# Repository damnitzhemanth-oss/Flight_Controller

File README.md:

# FLIGHT CONTROLLER - STM32F405

A custom 4 layer flight controller built from scratch for YSWS Pixl. This follows a hybrid approach of 50mm*50mm which is not normal for actual FCs on drone. This is only a **paper-design**. This has not been manufactured yet.

# Description 
This flight controller is unique in a way, unlike most of the FC's which skip Fuses to save space, this contains 3 fuses, making the room for human errors tiny.

The main MCU is STM32F405RGT6, this tiny thing has 1MB flash and 192KB ram and can easily run betaflight at full speed. With betaflight it can also do blackbox (memory) logging, IMU (gyroscope) and OSD (share details like altitude etc) simultaneously.

IMU I used for this project is ICM-42688-P which runs at 24 MHZ! It's a 6 axis gyroscope. I chose this because it is low noise (doesn't give false readings due to electrical noise) and gives reading in high resolution.

Then comes the blackbox which logs the data which is useful when the drone crashes or something so it is easier for us to point out errors. The exact module is W25Q128JVS,
~4 minutes of 2 kHz blackbox logging, or ~30 minutes at 500 Hz.

Watchdog-safe boot BOOT0 pull-down (R21) + BOOT1 pull-down (R25) MCU always boots from flash unless user says so. Sometimes when drone crashes MCU might repeatedly boot into USB mode and face continuous resets, but this mechanism ensures that, this aint going to happen.

No OSD: OSD is a chip that transmits data like altitude etc into the video, but most of the modern day digital cameras have this inbuilt. So I removed it.

No barometer: Same as OSD, most modern day GPS have barometer built in so there is no need of one on board.

2S - 6S input power, max 28V. And over current protection in built.

Reverse polarity protection,due to a P-FET on board even if the user connects + and - in reverse, power ain't gonna reach other parts,it's gonna stop at the P-Fet thus protecting rest of the FC.

USB ORing protection, with schkotty diode it ensures that USB and battery power won't fight or push power back.

5 independent UARTs, enough for connections GPS, Camera, etc with one spare.

4 pins for motors, with current and voltage measurement with dividers (a divider is a junction of Resistors which steps down the voltage/current and MCU multiplies it with a specific number,here 11 to get voltage and current readings).

Addressable RGB LED and two onboard LEDs indicating 5V and 3.3V with buzzer connections headers for audible output.

What makes it unique ? I built this board such that it is easy to debug, yes no board can work perfectly first time, this instead of saving space, i tried to make it more debuggable by adding multiple Testpoints. 

# Overview

This FC contains minimal architecture (as i am a rookie), it does not contain in built barometer or OSD.

# Architecture

```
Flight_Controller
├── PCB
│   ├── FlightController_Drone.csv
│   ├── FlightController_Drone.kicad_pcb
│   ├── FlightController_Drone.kicad_pro
│   ├── FlightController_Drone.kicad_sch
│   └── gerbers.zip
├── README.md
└── images
    ├── DRAFT
    │   ├── S10_2.png
    │   ├── S11_2.png
    │   ├── S12_2.png
    │   ├── S13_2.png
    │   ├── S1_1.png
    │   ├── S2_1.png
    │   ├── S3_1.png
    │   ├── S4_2.png
    │   ├── S4_P.png
    │   ├── S5_2.png
    │   ├── S6_2.png
    │   ├── S7_2.png
    │   ├── S8_2.png
    │   ├── S9_2.png
    │   └── SFull_2.png
    └── FINAL
        ├── 3D_PCB.png
        ├── 3D_PCB_B.png
        ├── 3D_PCB_HERO.png
        ├── Annotation 2026-10-11 182149.png
        ├── B_CU_PCB.png
        ├── DRC_DUMB.png
        ├── F_CU_PCB.png
        ├── F_PCB.png
        ├── In1_CU.png
        ├── In2_CU.png
        ├── S1.png
        ├── S10.png
        ├── S11.png
        ├── S12.png
        ├── S13.png
        ├── S2.png
        ├── S3.png
        ├── S4.png
        ├── S5.png
        ├── S6.png
        ├── S7.png
        ├── S8.png
        └── S9.png
```

# BOM
refer the .csv file in this repo under PCB.

# Gallery

**FOR MORE IMAGES PLEASE CHECK images FOLDER**  

# Note

DRC is giving weird errors about footprints touching each other which is fine until pads touch, so I moved them into warnings.

# AI usage
Ai was used only in one or two instances to verify netlist, this makes AI usage less than 5% for this project.

# License

MIT License and you are free to manufacture this board (ik no one will) but in case it dont work, inform me :)

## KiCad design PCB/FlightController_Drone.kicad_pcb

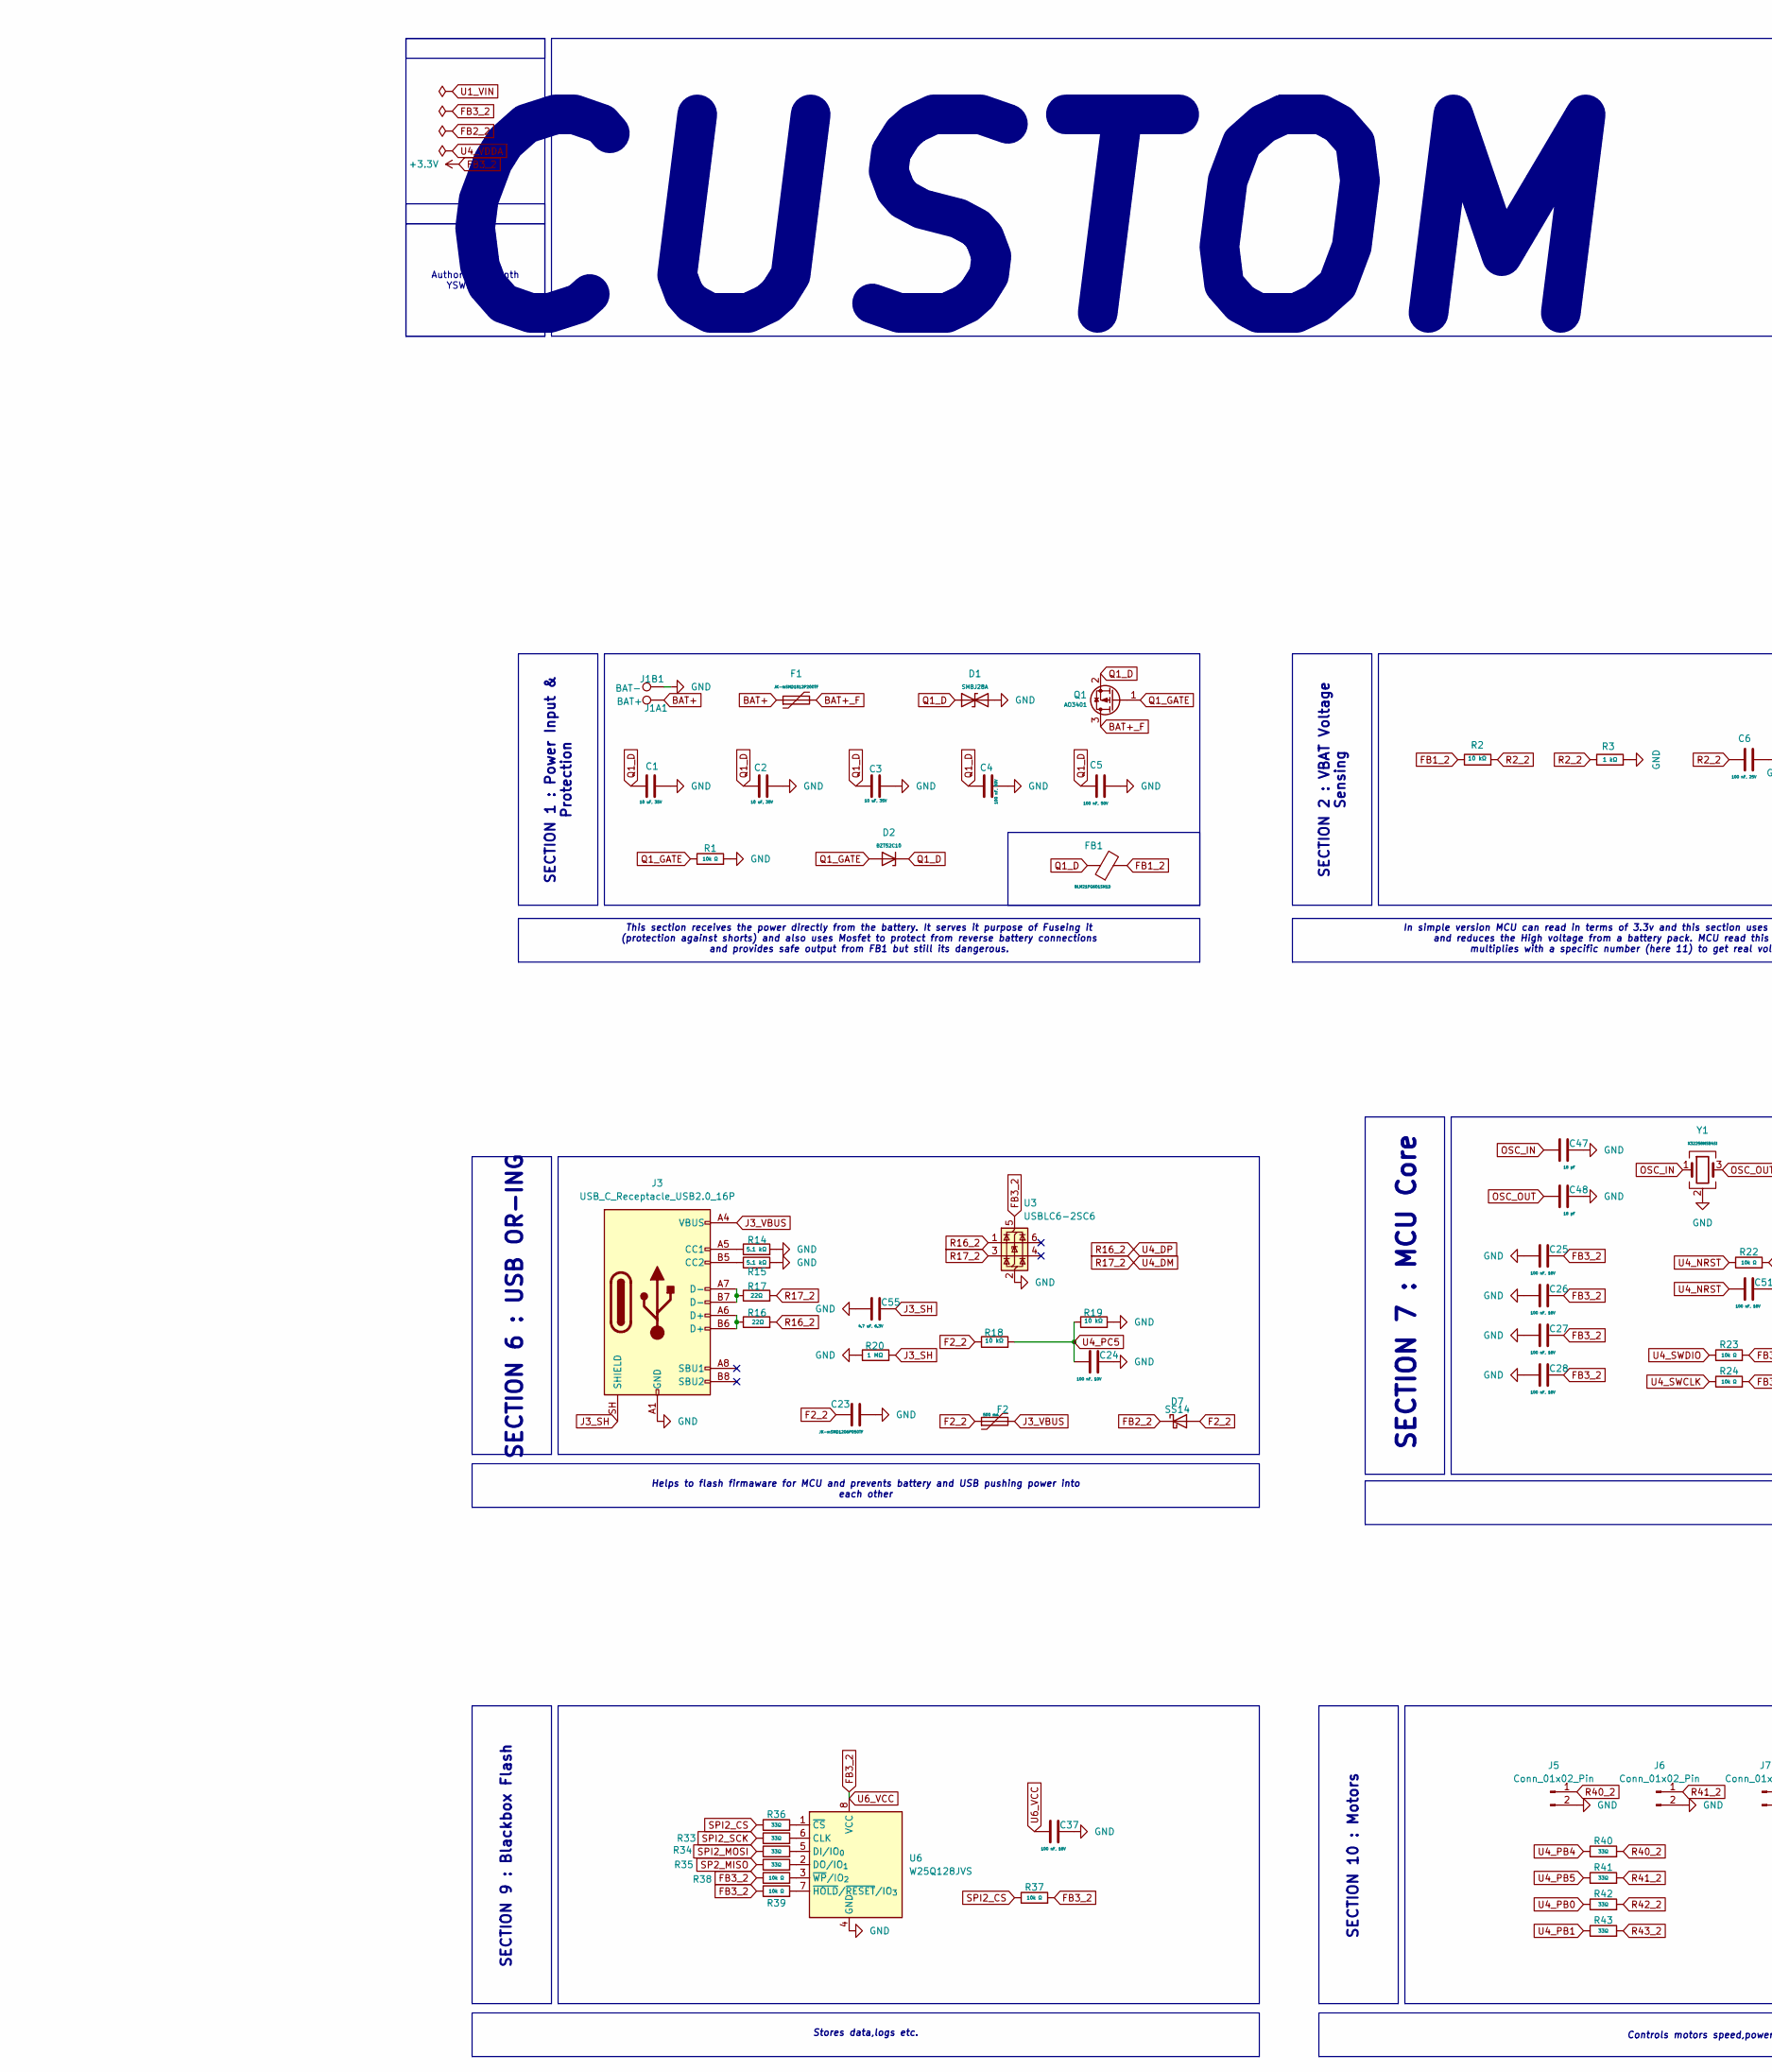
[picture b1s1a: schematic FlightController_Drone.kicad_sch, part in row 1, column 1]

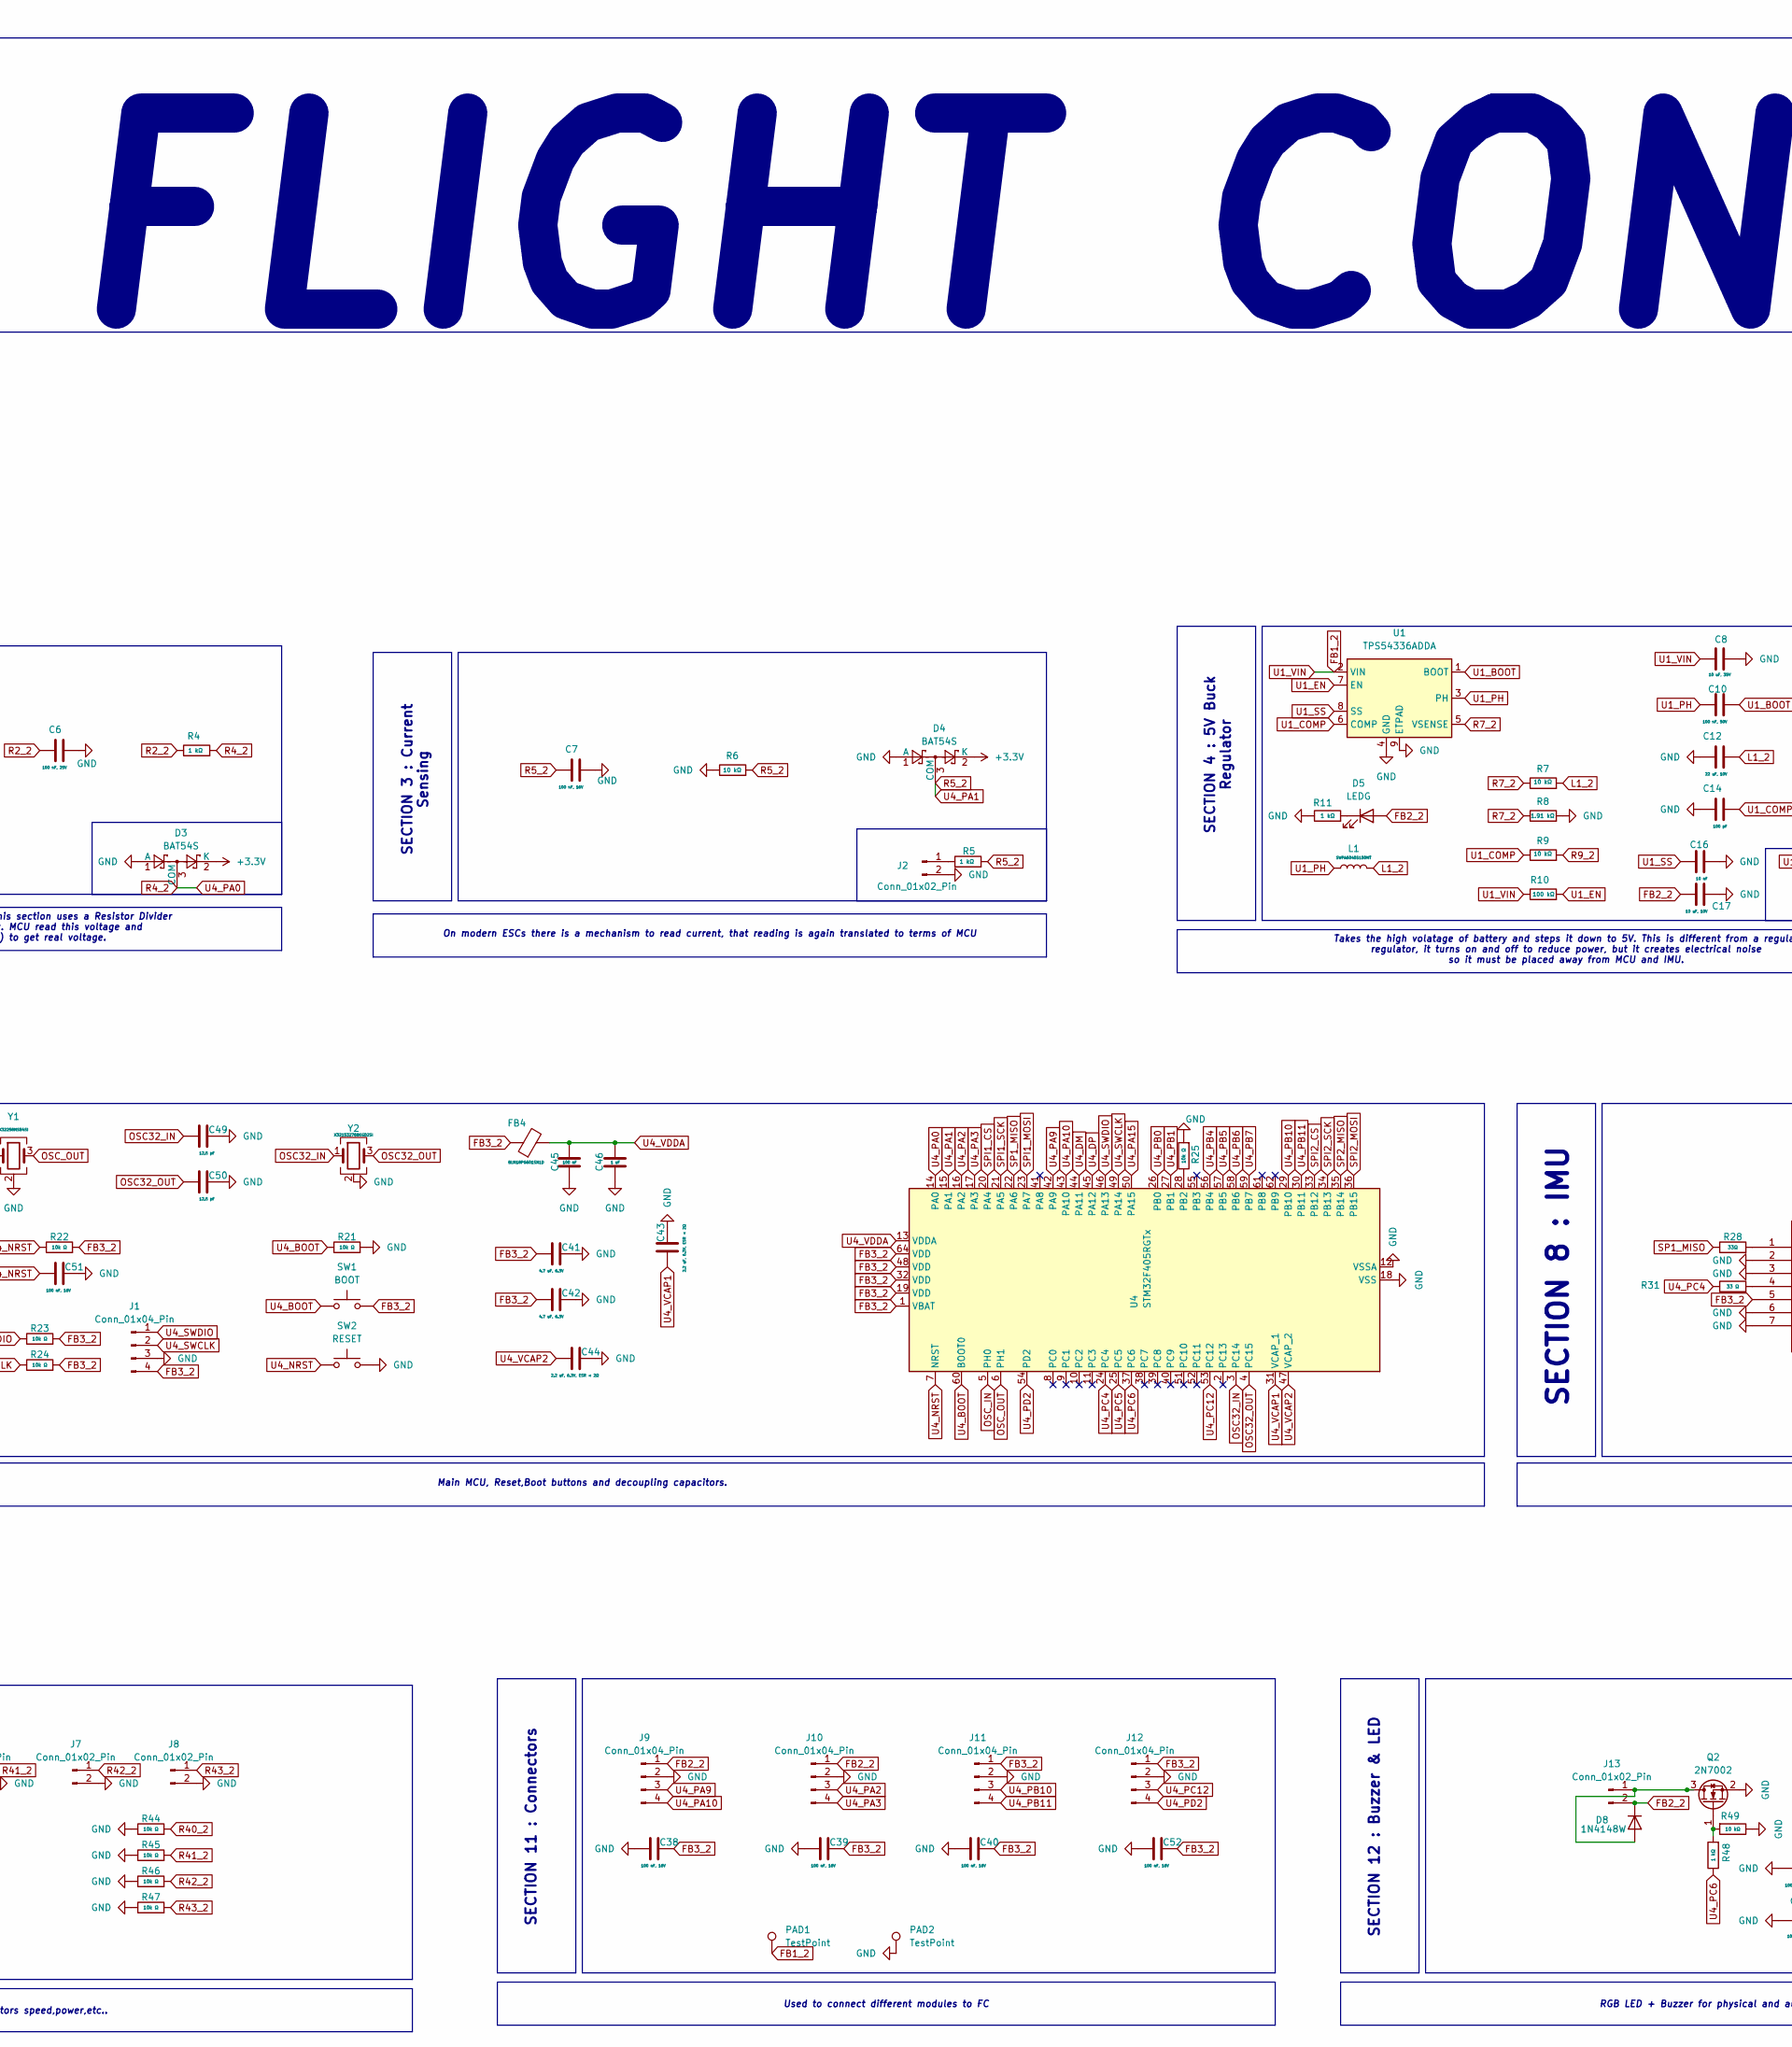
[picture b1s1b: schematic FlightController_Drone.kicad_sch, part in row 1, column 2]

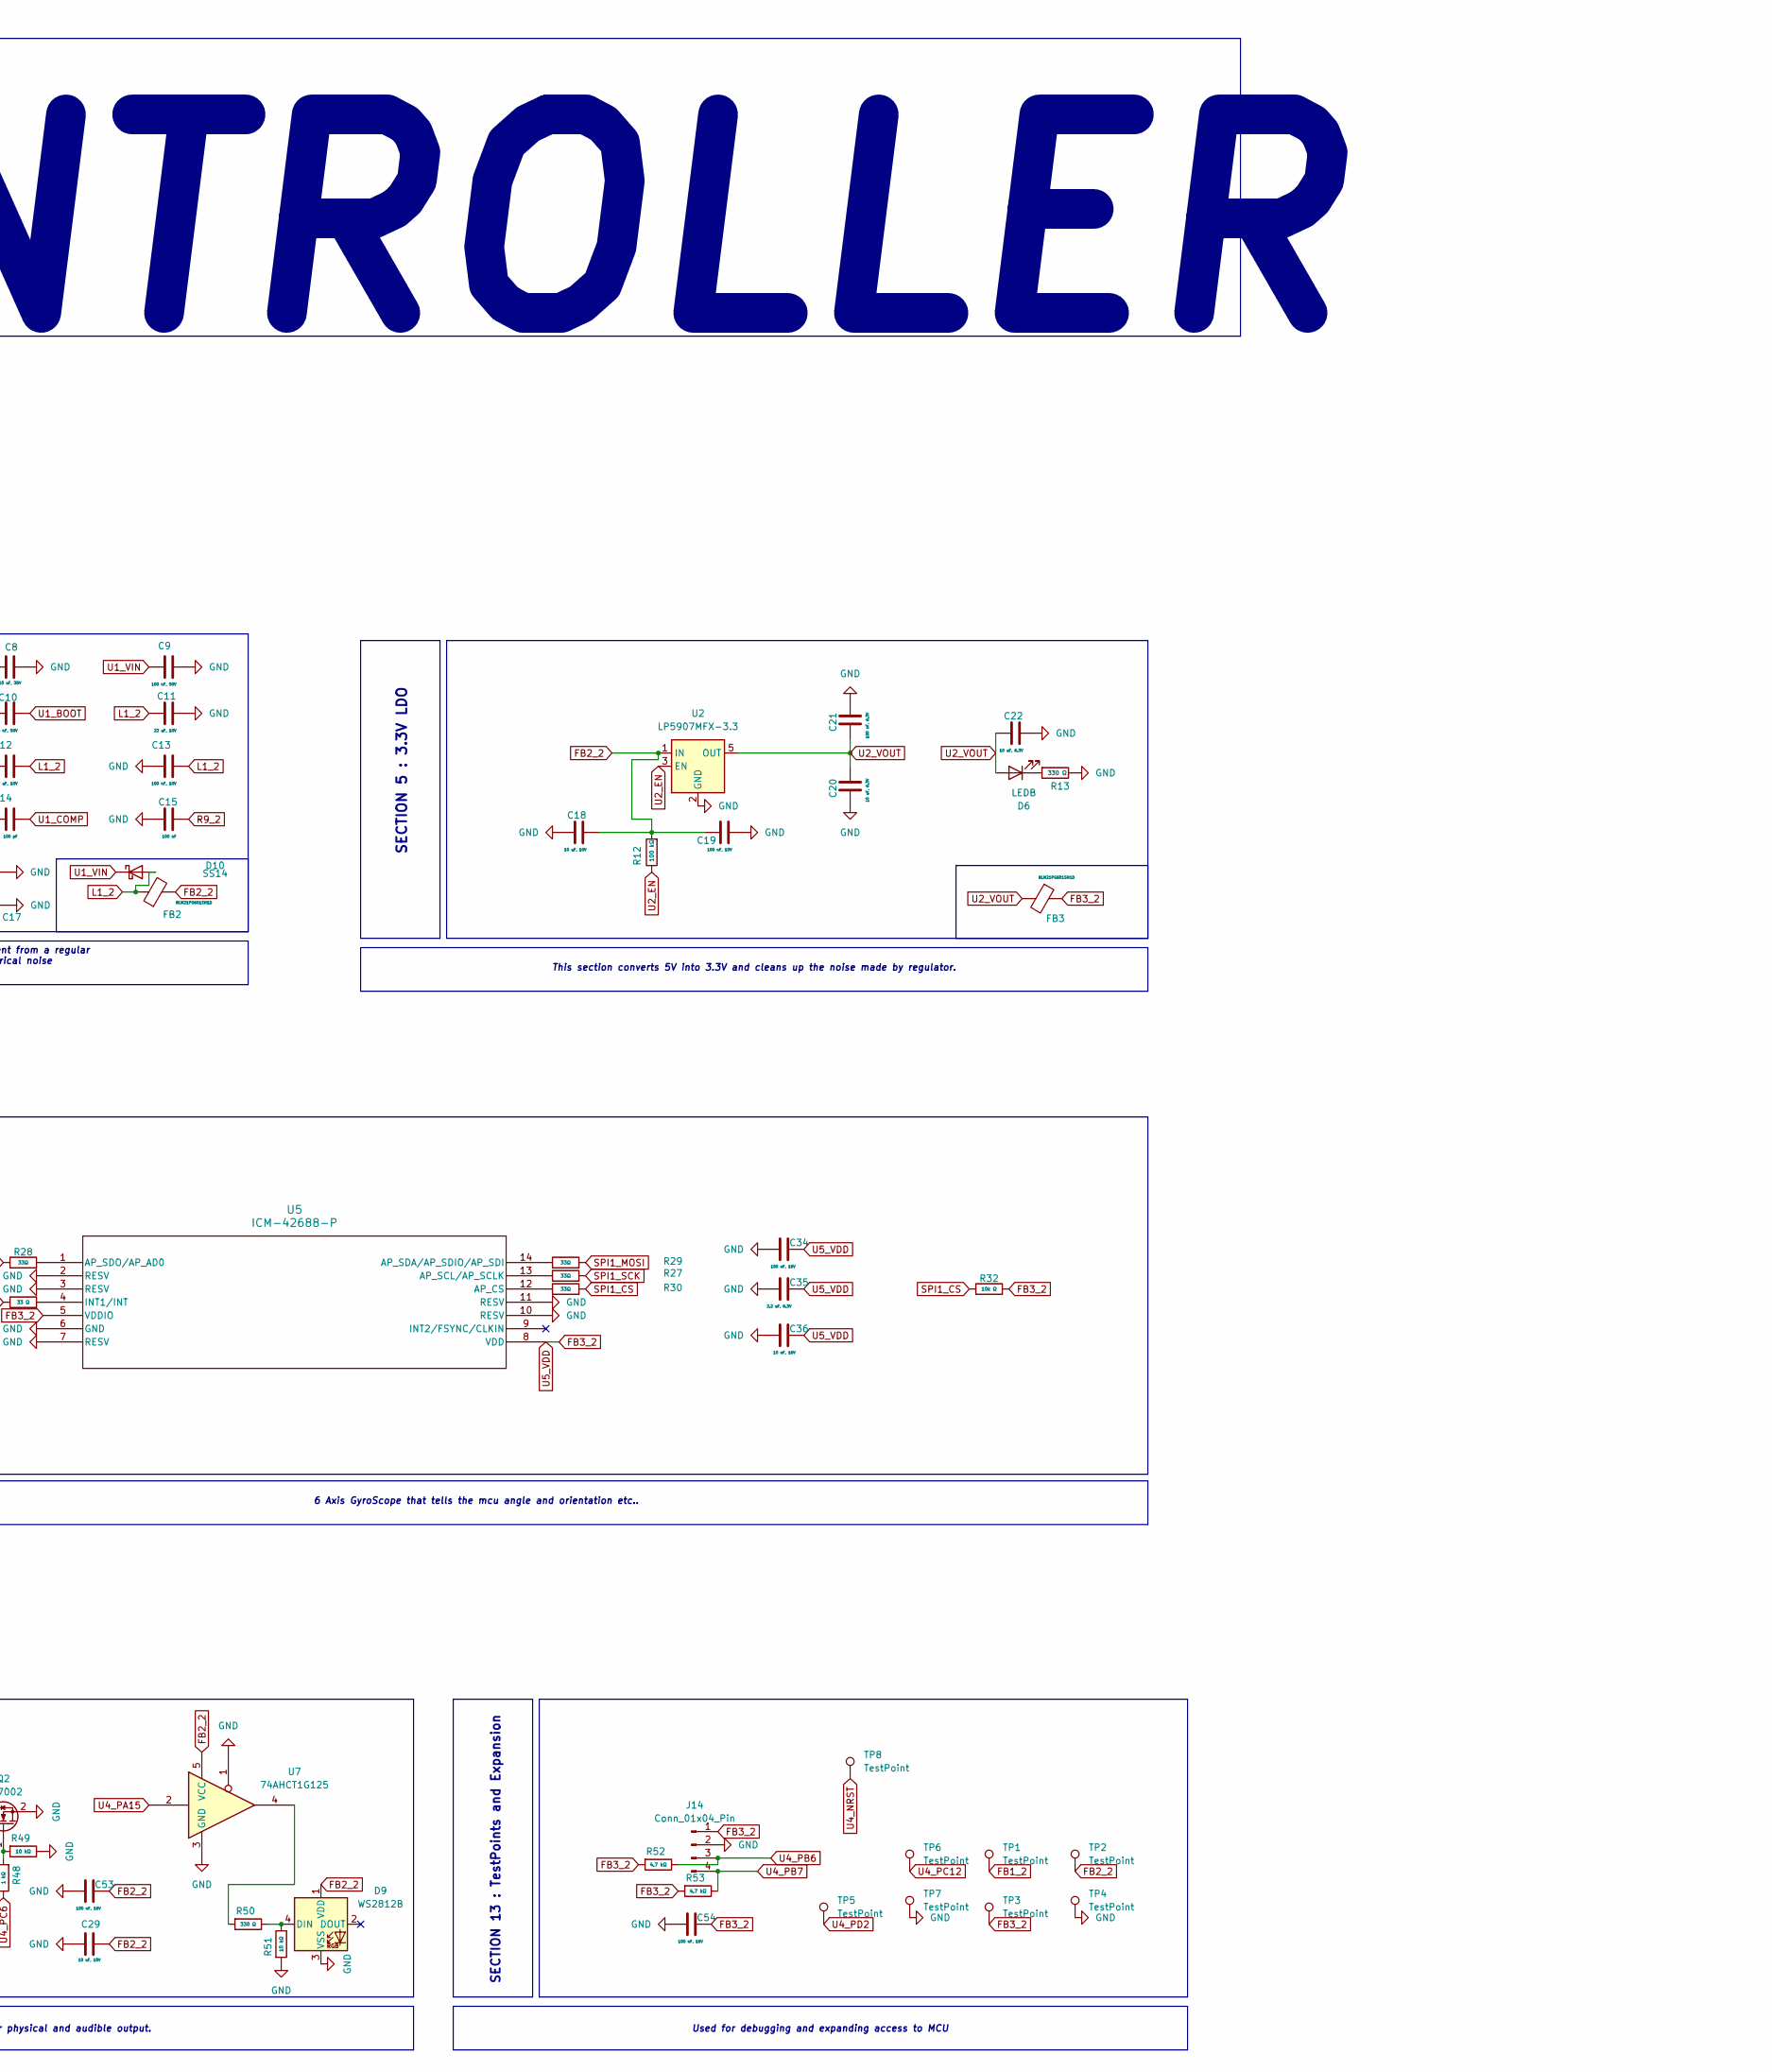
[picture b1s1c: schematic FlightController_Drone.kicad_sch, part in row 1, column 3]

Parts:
C1, C2, C3, C8: 10 uF, 35V; C_1206_3216Metric
C4, C5, C9, C10: 100 nF, 50V; C_0603_1608Metric
C6: 100 nF, 25V; C_0603_1608Metric
C7: 100 nF, 16V; C_0603_1608Metric
C11, C12: 22 uF, 10V; C_0805_2012Metric
C13, C19, C24: 100 nF, 10V; C_0603_1608Metric
C14: 100 pF; C_0603_1608Metric
C15: 100 nF; C_0603_1608Metric
C16: 10 nF; C_0603_1608Metric
C17, C18: 10 uF, 10V; C_0805_2012Metric
C20, C22: 10 uF, 6.3V; C_0805_2012Metric
C21: 100 nF, 6.3V; C_0805_2012Metric
C23: JK-mSMD1206P050TF; C_0603_1608Metric
C25, C26, C27, C28, C34, C37, C38, C39, C40, C51, C52, C53, C54: 100 nF, 16V; C_0402_1005Metric
C29: 10 uF, 10V; C_1206_3216Metric
C35: 2.2 uF, 6.3V; C_0603_1608Metric
C36: 10 nF, 16V; C_0402_1005Metric
C41, C42, C55: 4.7 uF, 6.3V; C_0603_1608Metric
C43, C44: 2.2 uF, 6.3V, ESR < 2Ω; C_0603_1608Metric
C45: 100 nF; C_0402_1005Metric
C46: 1 uF; C_0603_1608Metric
C47, C48: 18 pF; C_0402_1005Metric
C49, C50: 12.5 pF; C_0402_1005Metric
D1: SMBJ28A; D_SMB
D2: BZT52C10; D_SOD-323
D3, D4: BAT54S; SOT-23
D5: LEDG; LED_0603_1608Metric
D6: LEDB; LED_0603_1608Metric
D7, D10: SS14; D_SOD-323
D8: 1N4148W; D_SOD-323
D9: WS2812B; LED_WS2812B_PLCC4_5.0x5.0mm_P3.2mm
F1: JK-mSMD1812P200TF; Fuse_1812_4532Metric
F2: 500 mA; Fuse_1812_4532Metric
FB1, FB2, FB3: BLM21PG601SN1D; L_0805_2012Metric
FB4: BLM18PG601SN1D; L_0805_2012Metric
J1: Conn_01x04_Pin; PinHeader_1x04_P1.27mm_Vertical
J1A1: BAT+; TestPoint_Pad_D3.0mm
J1B1: BAT-; TestPoint_Pad_D3.0mm
J2, J5, J6, J7, J8, J13: Conn_01x02_Pin; PinHeader_1x02_P2.54mm_Vertical
J3: USB_C_Receptacle_USB2.0_16P; USB_C_Receptacle_HCTL_HC-TYPE-C-16P-01A
J9, J10, J11, J12, J14: Conn_01x04_Pin; JST_SH_SM04B-SRSS-TB_1x04-1MP_P1.00mm_Horizontal
L1: SWPA6045S150MT; L_6.3x6.3_H3
PAD1, PAD2: TestPoint; TestPoint_Pad_D2.0mm
Q1: AO3401; SOT-23
Q2: 2N7002; SOT-23
R1, R21, R22, R23, R24, R25, R32, R37, R38, R39, R44, R45, R46, R47: 10k Ω; R_0603_1608Metric
R2, R6, R7, R9, R18, R19: 10 kΩ; R_0603_1608Metric
R3, R4, R5, R11: 1 kΩ; R_0603_1608Metric
R8: 1.91 kΩ; R_0603_1608Metric
R10, R12: 100 kΩ; R_0603_1608Metric
R13: 330 Ω; R_0603_1608Metric
R14, R15: 5.1 kΩ; R_0603_1608Metric
R16, R17: 22Ω; R_0603_1608Metric
R20: 1 MΩ; R_0603_1608Metric
R27, R28, R29, R30, R33, R34, R35, R36, R40, R41, R42, R43: 33Ω; R_0402_1005Metric
R31: 33 Ω; R_0603_1608Metric
R48: 1 kΩ; R_0402_1005Metric
R49, R51: 10 kΩ; R_0402_1005Metric
R50: 330 Ω; R_0402_1005Metric
R52, R53: 4.7 kΩ; R_0402_1005Metric
SW1: BOOT; SW_SPST_TL3342
SW2: RESET; SW_SPST_TL3342
TP1, TP2, TP3, TP4, TP5, TP6, TP7, TP8: TestPoint; TestPoint_Pad_D1.5mm
U1: TPS54336ADDA; TI_SO-PowerPAD-8_ThermalVias
U2: LP5907MFX-3.3; SOT-23-5
U3: USBLC6-2SC6; SOT-23-6
U4: STM32F405RGTx; LQFP-64_10x10mm_P0.5mm
U5: ICM-42688-P; LGA14_2P5X3X0P91_TDK
U6: W25Q128JVS; SOIC-8_5.3x5.3mm_P1.27mm
U7: 74AHCT1G125; SOT-353_SC-70-5
Y1: X32258MSB4SI; Crystal_SMD_3225-4Pin_3.2x2.5mm
Y2: X321532768KGD2SI; Crystal_SMD_3225-4Pin_3.2x2.5mm

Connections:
BAT+: F1.1, J1A1.1 (1_1)
BAT+_F: F1.2, Q1.3 (D)
F2_2: C23.1, D7.2 (A), F2.1, R18.1
FB1_2: C8.1, C9.1, D10.1 (K), FB1.2, PAD1.1 (1_1), R2.1, R10.1, TP1.1 (1_1), U1.2 (VIN)
FB2_2: C17.1, C18.2, C19.1, C29.2, C53.2, D5.2 (A), D7.1 (K), D8.1 (K), D9.1 (VDD), FB2.2, J9.1, J10.1, J13.2, R12.2, TP2.1 (1_1), U2.1 (IN), U7.5 (VCC)
FB3_2: C25.2, C26.2, C27.2, C28.2, C34.2, C35.2, C36.2, C37.1, C38.2, C39.2, C40.2, C41.1, C42.1, C52.2, C54.2, D3.2 (K), D4.2 (K), FB3.1, FB4.1, J1.4, J11.1, J12.1, J14.1, R22.2, R23.2, R24.2, R32.2, R37.2, R38.1, R39.1, R52.2, R53.2, SW1.2, TP3.1 (1_1), U3.5 (VBUS), U4.1 (VBAT), U4.19 (VDD), U4.32 (VDD), U4.48 (VDD), U4.64 (VDD), U5.5 (VDDIO), U5.8 (VDD), U6.8 (VCC)
GND: C1.2, C2.2, C3.2, C4.2, C5.2, C6.2, C7.2, C8.2, C9.2, C11.2, C12.1, C13.1, C14.1, C15.1, C16.2, C17.2, C18.1, C19.2, C20.1, C21.2, C22.2, C23.2, C24.2, C25.1, C26.1, C27.1, C28.1, C29.1, C34.1, C35.1, C36.1, C37.2, C38.1, C39.1, C40.1, C41.2, C42.2, C43.2, C44.2, C45.1, C46.1, C47.2, C48.2, C49.2, C50.2, C51.2, C52.1, C53.1, C54.1, C55.1, D1.2 (A2), D3.1 (A), D4.1 (A), D9.3 (VSS), J1.3, J1B1.1 (1_1), J2.2, J3.A1 (GND), J3.A12 (GND), J3.B1 (GND), J3.B12 (GND), J5.2, J6.2, J7.2, J8.2, J9.2, J10.2, J11.2, J12.2, J14.2, PAD2.1 (1_1), Q2.2 (S), R1.2, R3.2, R6.1, R8.2, R11.1, R13.1, R14.2, R15.2, R19.2, R20.1, R21.2, R25.2, R44.1, R45.1, R46.1, R47.1, R49.1, R51.2, SW2.2, TP4.1 (1_1), TP7.1 (1_1), U1.4 (GND), U1.9 (ETPAD), U2.2 (GND), U3.2 (GND), U4.12 (VSSA), U4.18 (VSS), U4.63 (VSS), U5.2 (RESV), U5.3 (RESV), U5.6 (GND), U5.7 (RESV), U5.10 (RESV), U5.11 (RESV), U6.4 (GND), U7.1, U7.3 (GND), Y1.2 (G), Y1.4 (G), Y2.2 (G), Y2.4 (G)
J3_SH: C55.2, J3.SH (SHIELD), R20.2
J3_VBUS: F2.2, J3.A4 (VBUS), J3.A9 (VBUS), J3.B4 (VBUS), J3.B9 (VBUS)
L1_2: C11.1, C12.2, C13.2, D10.2 (A), FB2.1, L1.2, R7.2
unnamed: D5.1 (K), R11.2
unnamed: D6.1 (K), R13.2
unnamed: D8.2 (A), J13.1, Q2.3 (D)
unnamed: D9.4 (DIN), R50.1, R51.1
unnamed: J2.1, R5.1
unnamed: J3.A5 (CC1), R14.1
unnamed: J3.B5 (CC2), R15.1
unnamed: J3.A6 (D+), J3.B6 (D+), R16.1
unnamed: J3.A7 (D-), J3.B7 (D-), R17.1
unnamed: Q2.1 (G), R48.2, R49.2
unnamed: R50.2, U7.4
unnamed: R25.1, U4.28 (PB2)
unnamed: R30.1, U5.12 (AP_CS)
unnamed: R27.1, U5.13 (AP_SCL/AP_SCLK)
unnamed: R29.1, U5.14 (AP_SDA/AP_SDIO/AP_SDI)
unnamed: R28.2, U5.1 (AP_SDO/AP_AD0)
unnamed: R31.2, U5.4 (INT1/INT)
unnamed: R33.2, U6.6 (CLK)
unnamed: R34.2, U6.5 (DI/IO_{0})
unnamed: R35.2, U6.2 (DO/IO_{1})
unnamed: R36.2, U6.1 (~CS)
unnamed: R39.2, U6.7 (~HOLD/~RESET/IO_{3})
unnamed: R38.2, U6.3 (~WP/IO_{2})
OSC32_IN: C49.1, U4.3 (PC14), Y2.1
OSC32_OUT: C50.1, U4.4 (PC15), Y2.3
OSC_IN: C47.1, U4.5 (PH0), Y1.1
OSC_OUT: C48.1, U4.6 (PH1), Y1.3
Q1_D: C1.1, C2.1, C3.1, C4.1, C5.1, D1.1 (A1), D2.1 (K), FB1.1, Q1.2 (S)
Q1_GATE: D2.2 (A), Q1.1 (G), R1.1
R2_2: C6.1, R2.2, R3.1, R4.1
R4_2: D3.3 (COM), R4.2, U4.14 (PA0)
R5_2: C7.1, D4.3 (COM), R5.2, R6.2, U4.15 (PA1)
R7_2: R7.1, R8.1, U1.5 (VSENSE)
R9_2: C15.2, R9.2
R16_2: R16.2, U3.1 (I/O1), U4.45 (PA12)
R17_2: R17.2, U3.3 (I/O2), U4.44 (PA11)
R40_2: J5.1, R40.2, R44.2
R41_2: J6.1, R41.2, R45.2
R42_2: J7.1, R42.2, R46.2
R43_2: J8.1, R43.2, R47.2
SP1_MISO: R28.1, U4.22 (PA6)
SP2_MISO: R35.1, U4.35 (PB14)
SPI1_CS: R30.2, R32.1, U4.20 (PA4)
SPI1_MOSI: R29.2, U4.23 (PA7)
SPI1_SCK: R27.2, U4.21 (PA5)
SPI2_CS: R36.1, R37.1, U4.33 (PB12)
SPI2_MOSI: R34.1, U4.36 (PB15)
SPI2_SCK: R33.1, U4.34 (PB13)
U1_BOOT: C10.2, U1.1 (BOOT)
U1_COMP: C14.2, R9.1, U1.6 (COMP)
U1_EN: R10.2, U1.7 (EN)
U1_PH: C10.1, L1.1, U1.3 (PH)
U1_SS: C16.1, U1.8 (SS)
U2_EN: R12.1, U2.3 (EN)
U2_VOUT: C20.2, C21.1, C22.1, D6.2 (A), FB3.2, U2.5 (OUT)
U4_BOOT: R21.1, SW1.1, U4.60 (BOOT0)
U4_NRST: C51.1, R22.1, SW2.1, TP8.1, U4.7 (NRST)
U4_PA2: J10.3, U4.16 (PA2)
U4_PA3: J10.4, U4.17 (PA3)
U4_PA9: J9.3, U4.42 (PA9)
U4_PA10: J9.4, U4.43 (PA10)
U4_PA15: U4.50 (PA15), U7.2
U4_PB0: R42.1, U4.26 (PB0)
U4_PB1: R43.1, U4.27 (PB1)
U4_PB4: R40.1, U4.56 (PB4)
U4_PB5: R41.1, U4.57 (PB5)
U4_PB6: J14.3, R52.1, U4.58 (PB6)
U4_PB7: J14.4, R53.1, U4.59 (PB7)
U4_PB10: J11.3, U4.29 (PB10)
U4_PB11: J11.4, U4.30 (PB11)
U4_PC4: R31.1, U4.24 (PC4)
U4_PC5: C24.1, R18.2, R19.1, U4.25 (PC5)
U4_PC6: R48.1, U4.37 (PC6)
U4_PC12: J12.3, TP6.1 (1_1), U4.53 (PC12)
U4_PD2: J12.4, TP5.1 (1_1), U4.54 (PD2)
U4_SWCLK: J1.2, R24.1, U4.49 (PA14)
U4_SWDIO: J1.1, R23.1, U4.46 (PA13)
U4_VCAP1: C43.1, U4.31 (VCAP_1)
U4_VCAP2: C44.1, U4.47 (VCAP_2)
U4_VDDA: C45.2, C46.2, FB4.2, U4.13 (VDDA)

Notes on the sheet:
SECTION 6 : USB OR-ING
SECTION 12 : Buzzer & LED
SECTION 4 : 5V Buck Regulator
SECTION 1 : Power Input & Protection
CUSTOM FLIGHT CONTROLLER
SECTION 3 : Current Sensing
SECTION 8 : IMU
SECTION 10 : Motors
SECTION 7 : MCU Core
SECTION 9 : Blackbox Flash
SECTION 2 : VBAT Voltage Sensing
SECTION 11 : Connectors
SECTION 5 : 3.3V LDO
Details
SECTION 13 : TestPoints and Expansion
Main MCU, Reset,Boot buttons and decoupling capacitors.
Helps to flash firmaware for MCU and prevents battery and USB pushing power into each other
In simple version MCU can read in terms of 3.3v and this section uses a Resistor Divider and reduces the High voltage from a battery pack. MCU read this voltage and multiplies with a specific number (here 11) to get real voltage.
This section receives the power directly from the battery. It serves it purpose of Fuseing it (protection against shorts) and also uses Mosfet to protect from reverse battery connections and provides safe output from FB1 but still its dangerous.
6 Axis GyroScope that tells the mcu angle and orientation etc..
This section converts 5V into 3.3V and cleans up the noise made by regulator.
Takes the high volatage of battery and steps it down to 5V. This is different from a regular regulator, it turns on and off to reduce power, but it creates electrical noise so it must be placed away from MCU and IMU.
Used to connect different modules to FC
Stores data,logs etc.
Author : Hemanth YSWS : Pixl
On modern ESCs there is a mechanism to read current, that reading is again translated to terms of MCU
Controls motors speed,power,etc..
RGB LED + Buzzer for physical and audible output.
Used for debugging and expanding access to MCU

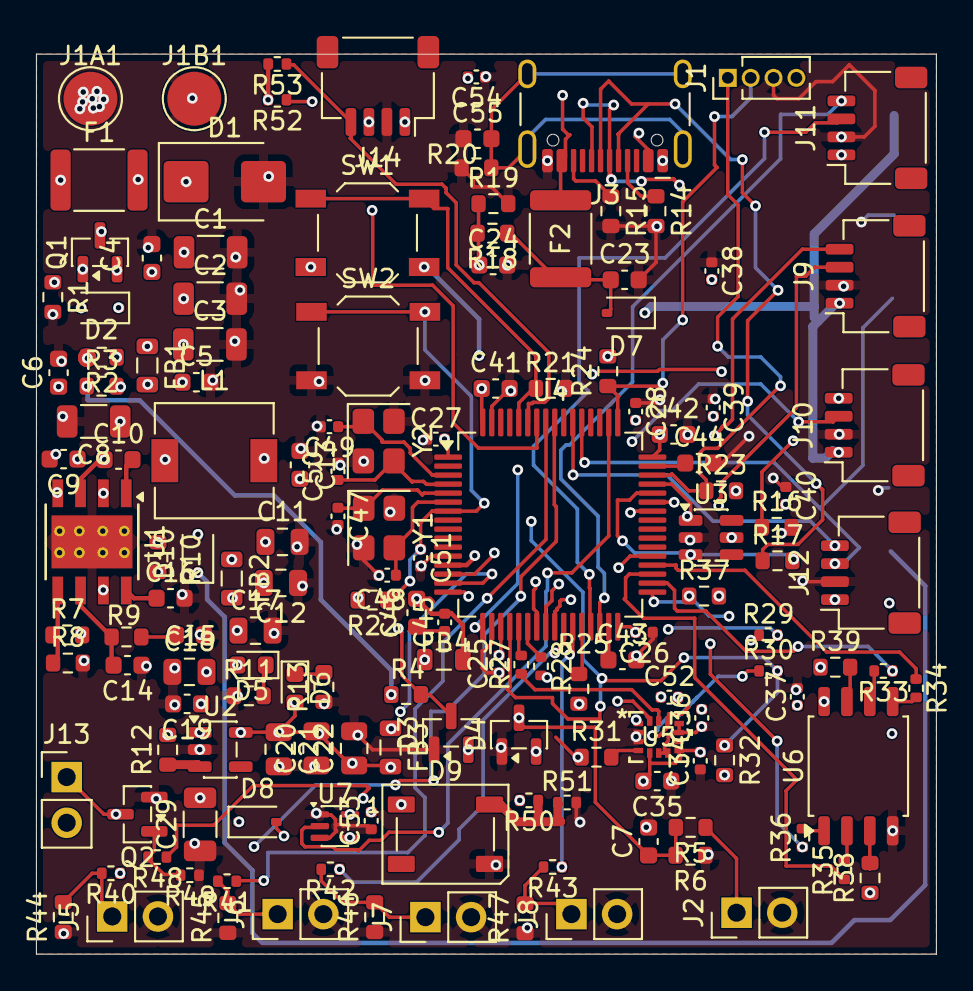
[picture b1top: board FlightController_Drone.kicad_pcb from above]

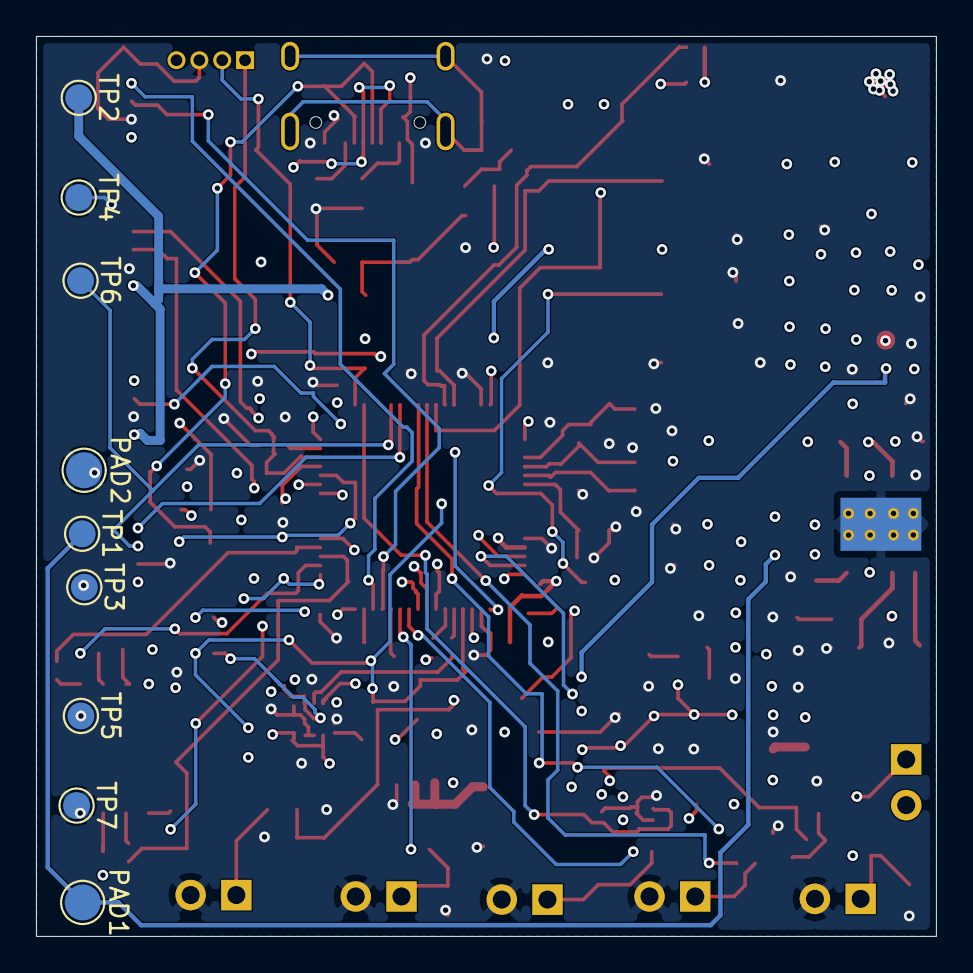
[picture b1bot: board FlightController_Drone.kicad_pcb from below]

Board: 4 copper layers, 50.0 x 50.0 mm, 157 parts (9 on the bottom side), 90 nets.
